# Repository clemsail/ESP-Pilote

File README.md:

# ESP-Pilote

Ceci est un projet autor d'esp easy pour gérer un fil pilote de chauffage en wifi 
avec capteur de temperature, capteur de courant et ES deportée

liste composant :
1x Alim 3.3v HLK-PM03
http://www.ebay.fr/itm/252533336629?_trksid=p2057872.m2749.l2649

1x ESP8266 12e
1x Fusible 500mA (exemple : http://fr.farnell.com/multicomp/mst-500ma-250v/fusible-radial-action-lente-bbas/dp/1566097)

2x Diode 1N4007
2x optotriac TLP168J

1x capteur de courant 
ALLEGRO MICROSYSTEMS - ACS758LCB-050B-PFF-T - IC, ACTUEL CAPTEUR, 50A, 3CB

1x condensateur 0.1µF
1x resistance 4.7k
2x resistance 470
1x capteur de temperature dallas ds18b20

des pinoche ecartement 2.54

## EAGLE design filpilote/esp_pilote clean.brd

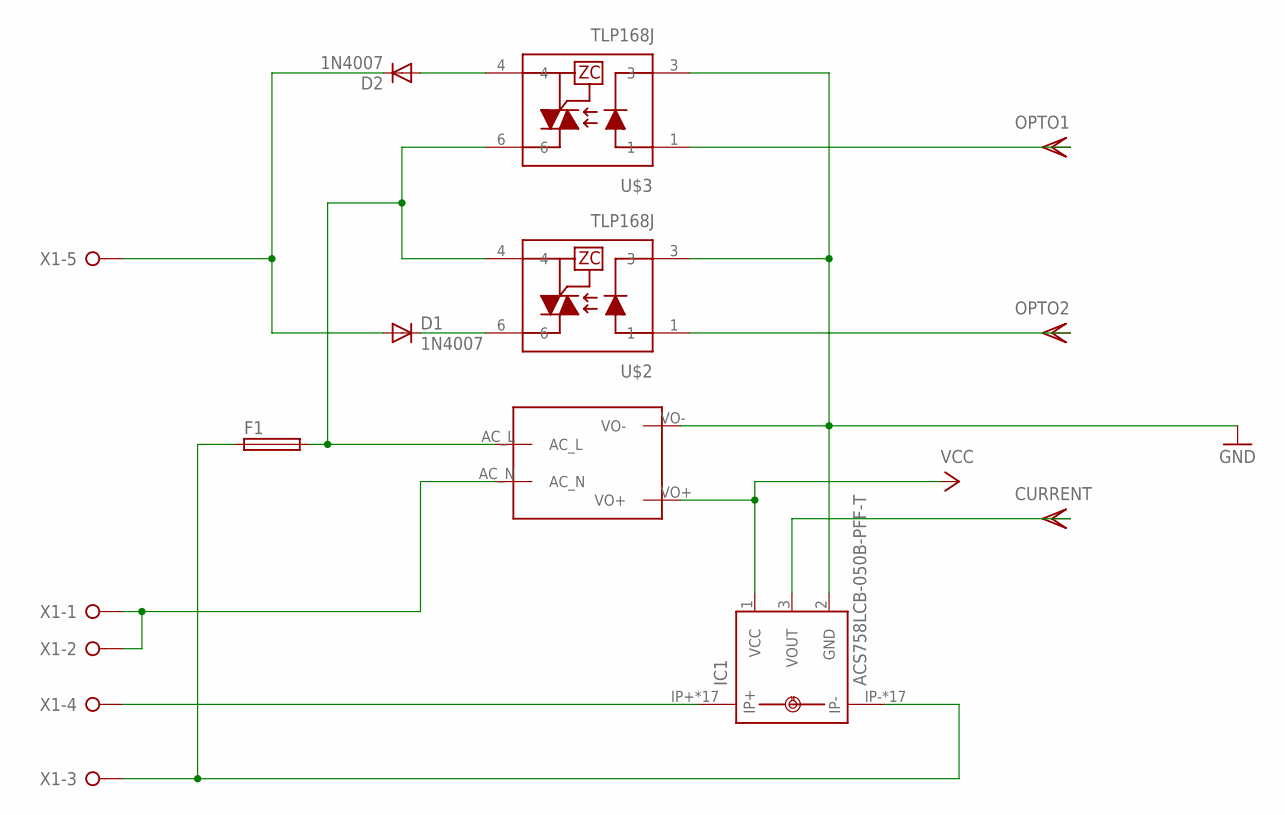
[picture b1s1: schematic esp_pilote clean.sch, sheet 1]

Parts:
D1, D2: 1N4007; DO41-10
F1: 19560
IC1: ACS758LCB-050B-PFF-T; CB-PFF
U$1: MAINS_CONVERTERS; HLK-PM01
U$2, U$3: TLP168J; MFSOP-4
X1: W237-05P; W237-5P

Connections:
230FUSED: F1.2, U$1.AC_L, U$2.4, U$3.6
230OUT: F1.1, IC1.IP-, IC1.IP-@2 (IP-), IC1.IP-@3 (IP-), IC1.IP-@4 (IP-), IC1.IP-@5 (IP-), IC1.IP-@6 (IP-), IC1.IP-@7 (IP-), IC1.IP-@8 (IP-), IC1.IP-@9 (IP-), IC1.IP-@10 (IP-), IC1.IP-@11 (IP-), IC1.IP-@12 (IP-), IC1.IP-@13 (IP-), IC1.IP-@14 (IP-), IC1.IP-@15 (IP-), IC1.IP-@16 (IP-), IC1.IP-@17 (IP-), X1.3
CURENT: IC1.3 (VOUT); also elsewhere on the board
GND: IC1.2 (GND), U$1.VO-, U$2.3, U$3.3; also elsewhere on the board
unnamed: IC1.IP+, IC1.IP+@2 (IP+), IC1.IP+@3 (IP+), IC1.IP+@4 (IP+), IC1.IP+@5 (IP+), IC1.IP+@6 (IP+), IC1.IP+@7 (IP+), IC1.IP+@8 (IP+), IC1.IP+@9 (IP+), IC1.IP+@10 (IP+), IC1.IP+@11 (IP+), IC1.IP+@12 (IP+), IC1.IP+@13 (IP+), IC1.IP+@14 (IP+), IC1.IP+@15 (IP+), IC1.IP+@16 (IP+), IC1.IP+@17 (IP+), X1.4
NEUTRAL: U$1.AC_N, X1.1, X1.2
OPTO1: U$3.1; also elsewhere on the board
OPTO2: U$2.1; also elsewhere on the board
OPTO_O1: D2.A, U$3.4
OPTO_O2: D1.C, U$2.6
PILOTE: D1.A, D2.C, X1.5
VCC: IC1.1 (VCC), U$1.VO+; also elsewhere on the board

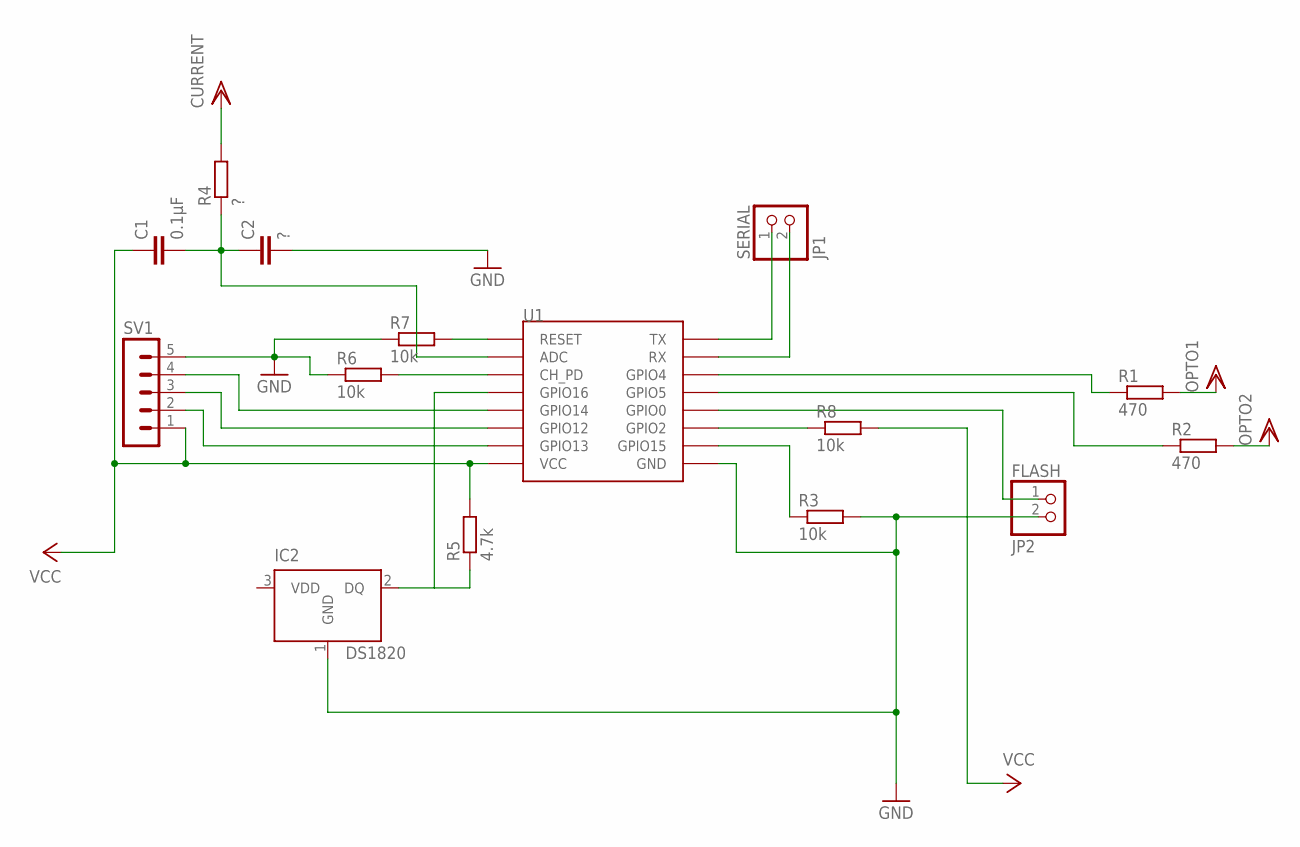
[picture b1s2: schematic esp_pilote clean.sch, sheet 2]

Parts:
C1: 0.1µF; C5B3.5
C2: ?; C5B3.5
FLASH: JP2; 1X02
IC2: DS1820; TO-92
R1, R2: 470; 0207/10
R3, R6, R7, R8: 10k; 0207/10
R4: ?; 0207/10
R5: 4.7k; 0207/10
SERIAL: JP1; 1X02
SV1: MA05-1
U1: ESP12SMD; ESP12-SMD

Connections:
CH_PD: R6.2, U1.CH_PD
CURENT: R4.2; also elsewhere on the board
CURRENT: C1.2, C2.1, R4.1, U1.ADC
DS18B20: IC2.2 (DQ), R5.1, U1.GPIO16
GND: C2.2, FLASH.2, IC2.1 (GND), R3.2, R6.1, R7.1, SV1.5, U1.GND; also elsewhere on the board
GP12: SV1.3, U1.GPIO12
GP13: SV1.2, U1.GPIO13
GP14: SV1.4, U1.GPIO14
unnamed: SERIAL.1, U1.TXD0 (TX)
unnamed: SERIAL.2, U1.RXD0 (RX)
unnamed: FLASH.1, U1.GPIO0
unnamed: R3.1, U1.GPIO15
unnamed: R8.1, U1.GPIO2
OPTO1: R1.2; also elsewhere on the board
OPTO1_OUT: R1.1, U1.GPIO4
OPTO2: R2.2; also elsewhere on the board
OPTO2_OUT: R2.1, U1.GPIO5
RST: R7.2, U1.RESET
VCC: C1.1, R5.2, R8.2, SV1.1, U1.VCC; also elsewhere on the board

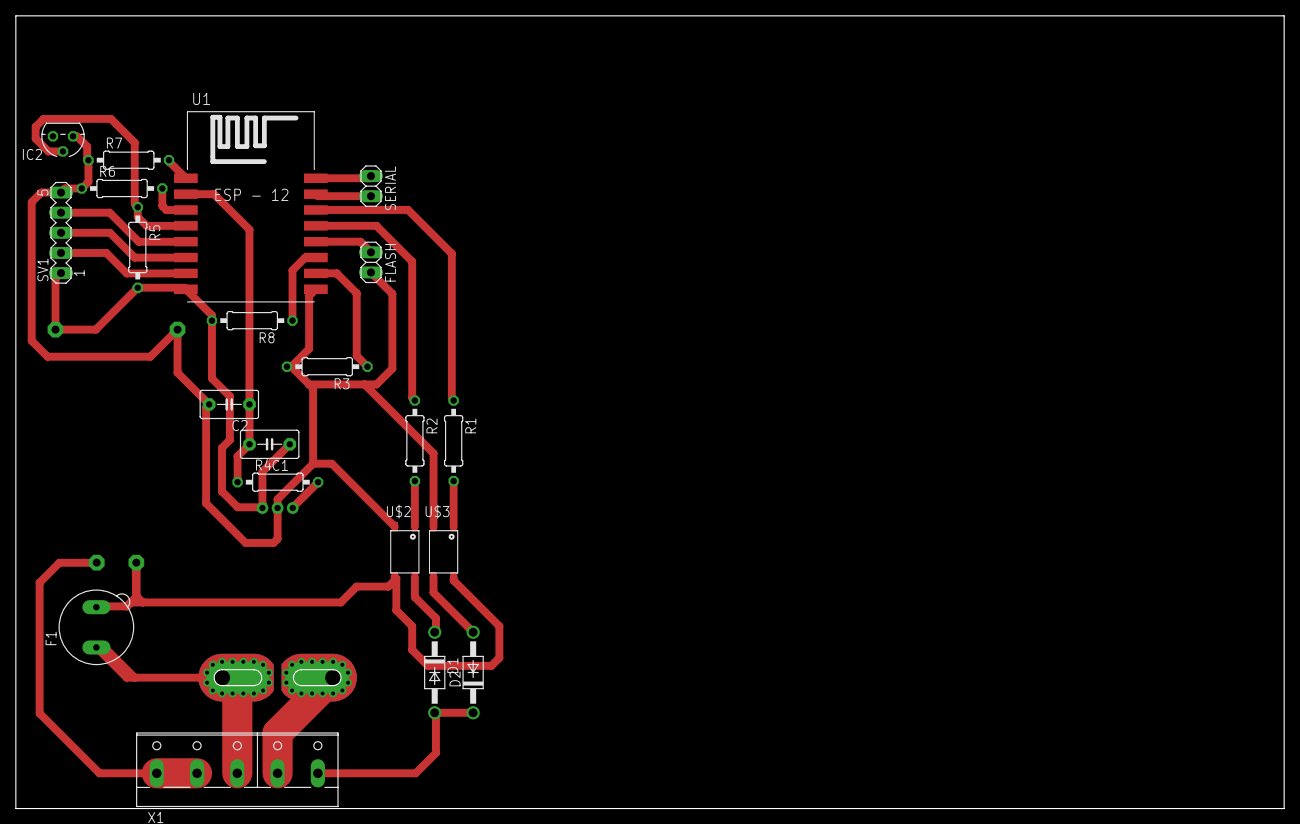
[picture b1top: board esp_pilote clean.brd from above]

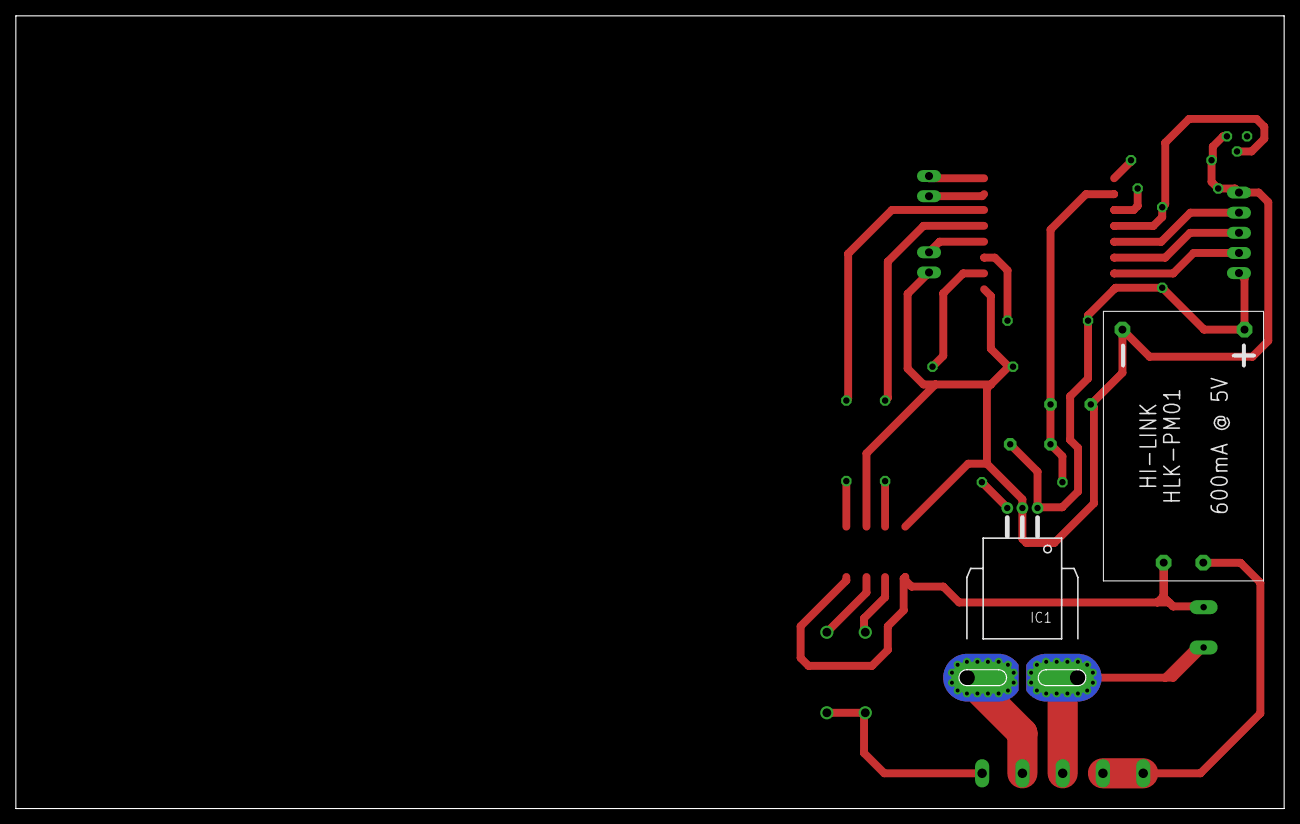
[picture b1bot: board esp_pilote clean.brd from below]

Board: 2 copper layers, 160.0 x 100.0 mm, 23 parts (2 on the bottom side), 26 nets.

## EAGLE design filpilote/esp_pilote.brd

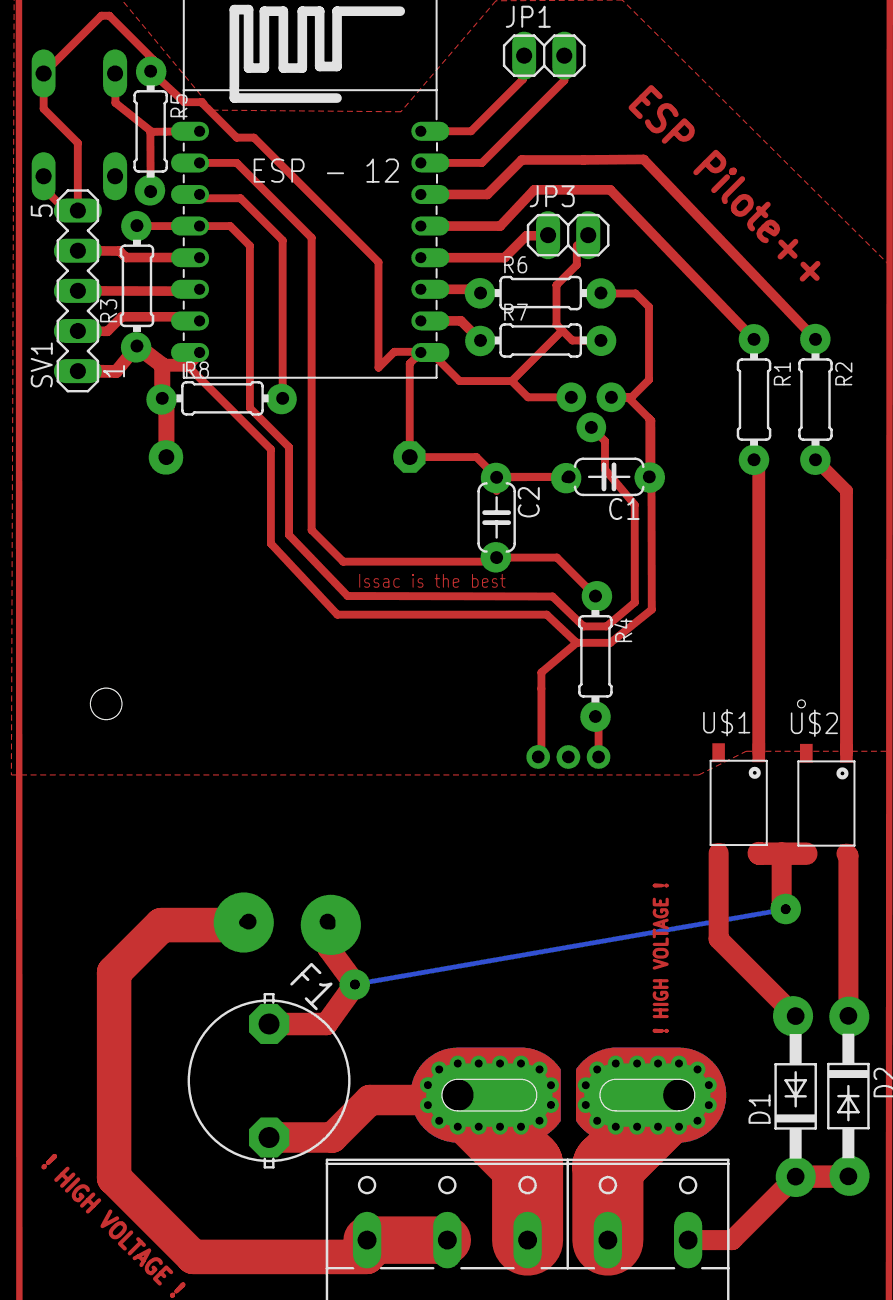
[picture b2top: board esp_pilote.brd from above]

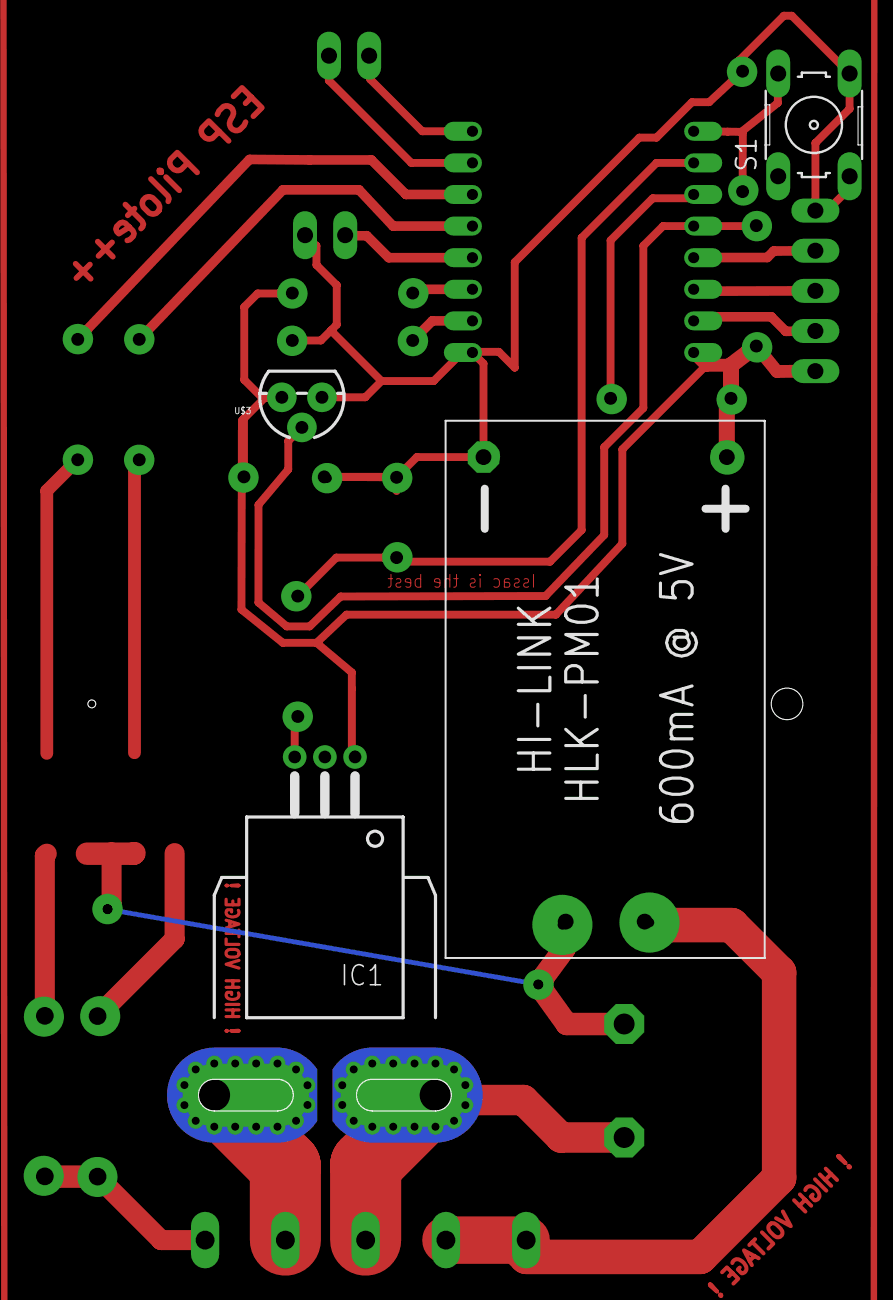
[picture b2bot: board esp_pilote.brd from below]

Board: 2 copper layers, 24 parts (4 on the bottom side), 26 nets.

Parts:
C1: 0,1µf; C050-024X044
C2: ?; C050-024X044
D1, D2: 1N4007; DO41-10
F1: 0,5A; 19559
IC1: ACS758LCB-050B-PFF-T; CB-PFF
JP1, JP3: 1X02
MDL1: ESP; ESP12
R1, R2: 470; 0204/7
R3: 4.7k; 0204/7
R4: ?; 0204/7
R5, R6, R7, R8: 10k; 0204/7
S1: B3F-10XX
SV1: MA05-1
U$1, U$2: TLP168J; MFSOP-4
U$3: TEMPERATURE-SENSOR; TO-92
U$4: MAINS_CONVERTERS; HLK-PM01
X1: W237-5P

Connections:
230FUSED: F1.1, U$1.6, U$2.4, U$4.AC_L
230IN: F1.2, IC1.IP-, IC1.IP-@2, IC1.IP-@3, IC1.IP-@4, IC1.IP-@5, IC1.IP-@6, IC1.IP-@7, IC1.IP-@8, IC1.IP-@9, IC1.IP-@10, IC1.IP-@11, IC1.IP-@12, IC1.IP-@13, IC1.IP-@14, IC1.IP-@15, IC1.IP-@16, IC1.IP-@17, X1.3
230OUT: IC1.IP+, IC1.IP+@2, IC1.IP+@3, IC1.IP+@4, IC1.IP+@5, IC1.IP+@6, IC1.IP+@7, IC1.IP+@8, IC1.IP+@9, IC1.IP+@10, IC1.IP+@11, IC1.IP+@12, IC1.IP+@13, IC1.IP+@14, IC1.IP+@15, IC1.IP+@16, IC1.IP+@17, X1.4
CURRENT: C2.2, MDL1.ADC, R4.1
DS18B20: MDL1.GPIO16, R3.2, U$3.2
GND: C1.2, C2.1, IC1.2, JP3.2, MDL1.GND, R5.1, R7.2, S1.3, S1.4, SV1.5, U$1.3, U$2.3, U$3.1, U$4.VO-
unnamed: D2.C, U$2.6
unnamed: R1.2, U$1.1
unnamed: IC1.3, R4.2
unnamed: D1.A, U$1.4
unnamed: MDL1.GPIO13, SV1.2
unnamed: MDL1.GPIO12, SV1.3
unnamed: MDL1.GPIO14, SV1.4
unnamed: R2.2, U$2.1
unnamed: MDL1.GPIO5, R1.1
unnamed: MDL1.GPIO4, R2.1
unnamed: MDL1.RESET, R5.2, S1.2
unnamed: JP1.1, MDL1.TX
unnamed: JP1.2, MDL1.RX
unnamed: MDL1.CH_PD, R8.2
unnamed: MDL1.GPIO2, R6.1
unnamed: MDL1.GPIO15, R7.1
unnamed: JP3.1, MDL1.GPIO0
NEUTRAL: U$4.AC_N, X1.1, X1.2
PILOTE: D1.C, D2.A, X1.5
VCC: C1.1, IC1.1, MDL1.VCC, R3.1, R6.2, R8.1, SV1.1, U$3.3, U$4.VO+

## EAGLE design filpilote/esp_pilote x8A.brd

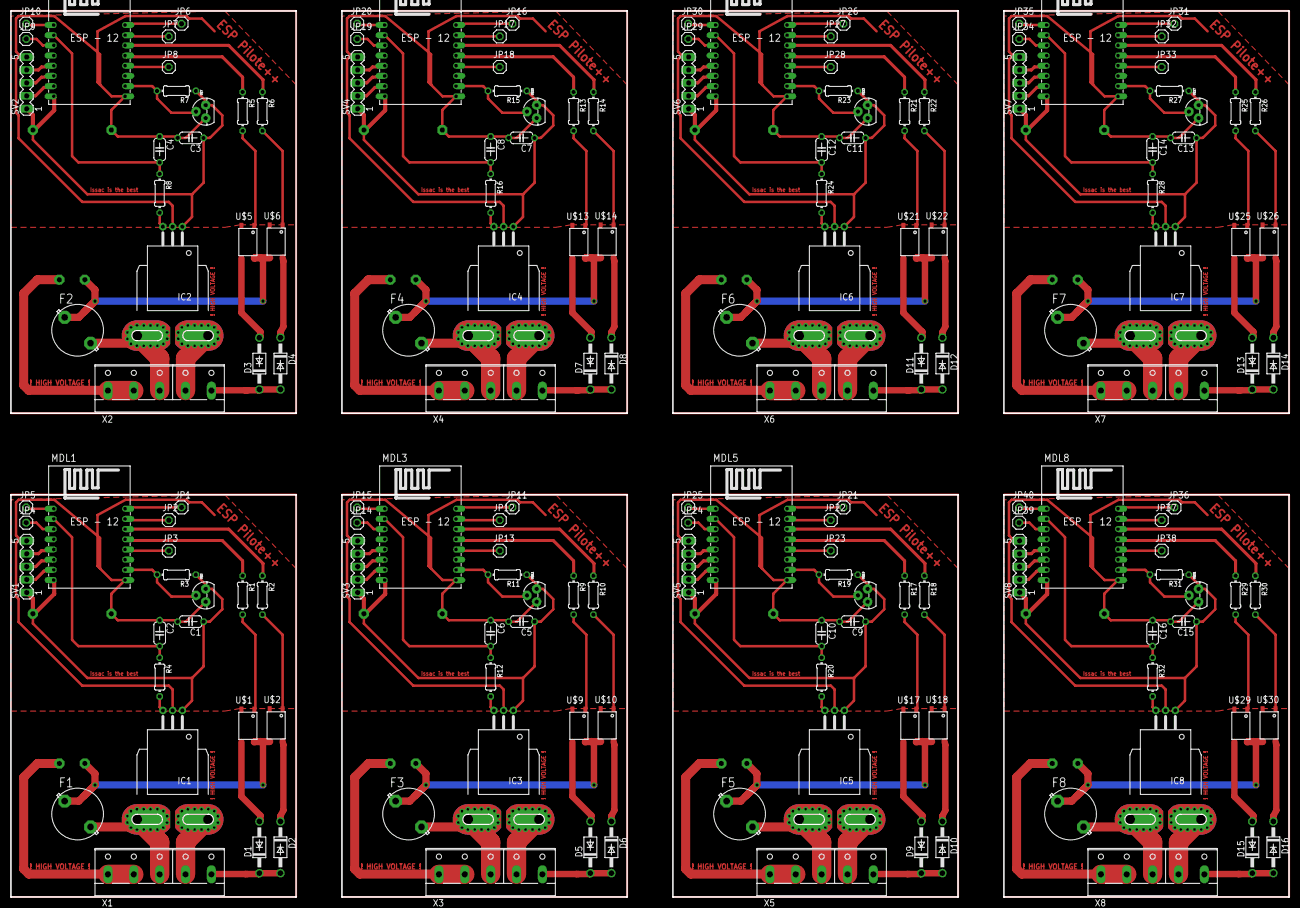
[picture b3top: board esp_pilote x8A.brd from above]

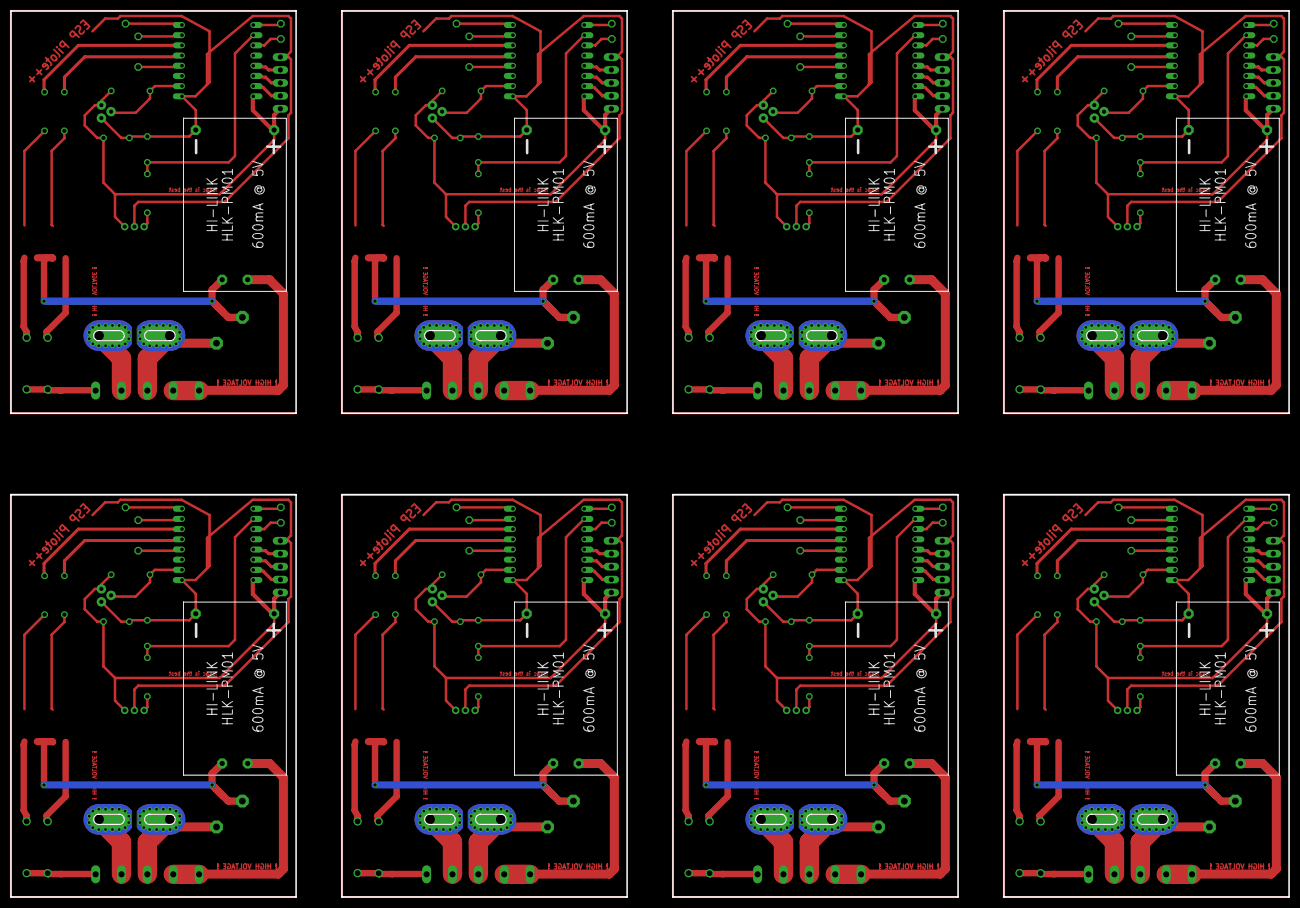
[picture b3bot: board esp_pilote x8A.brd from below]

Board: 2 copper layers, 251.0 x 174.0 mm, 176 parts (8 on the bottom side), 192 nets.

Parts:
C1, C3, C5, C7, C9, C11, C13, C15: 0,1µf; C050-024X044
C2, C4, C6, C8, C10, C12, C14, C16: ?; C050-024X044
D1, D2, D3, D4, D5, D6, D7, D8, D9, D10, D11, D12, D13, D14, D15, D16: 1N4007; DO41-10
F1, F2, F3, F4, F5, F6, F7, F8: 0,5A; 19559
IC1, IC2, IC3, IC4, IC5, IC6, IC7, IC8: ACS758LCB-050B-PFF-T; CB-PFF
JP1, JP2, JP3, JP4, JP5, JP6, JP7, JP8, JP9, JP10, JP11, JP12, JP13, JP14, JP15, JP16, JP17, JP18, JP19, JP20, JP21, JP22, JP23, JP24, JP25, JP26, JP27, JP28, JP29, JP30, JP31, JP32, JP33, JP34, JP35, JP36, JP37, JP38, JP39, JP40: 1X01
MDL1, MDL2, MDL3, MDL4, MDL5, MDL6, MDL7, MDL8: ESP; ESP12
R1, R2, R5, R6, R9, R10, R13, R14, R17, R18, R21, R22, R25, R26, R29, R30: 470; 0204/7
R3, R7, R11, R15, R19, R23, R27, R31: 4.7k; 0204/7
R4, R8, R12, R16, R20, R24, R28, R32: ?; 0204/7
SV1, SV2, SV3, SV4, SV5, SV6, SV7, SV8: MA05-1
U$1, U$2, U$5, U$6, U$9, U$10, U$13, U$14, U$17, U$18, U$21, U$22, U$25, U$26, U$29, U$30: TLP168J; MFSOP-4
U$3, U$7, U$11, U$15, U$19, U$23, U$27, U$31: TEMPERATURE-SENSOR; TO-92
U$4, U$8, U$12, U$16, U$20, U$24, U$28, U$32: MAINS_CONVERTERS; HLK-PM01
X1, X2, X3, X4, X5, X6, X7, X8: W237-5P

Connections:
230FUSED: F1.1, U$1.6, U$2.4, U$4.AC_L
230FUSED1: F2.1, U$5.6, U$6.4, U$8.AC_L
230FUSED2: F3.1, U$9.6, U$10.4, U$12.AC_L
230FUSED3: F4.1, U$13.6, U$14.4, U$16.AC_L
230FUSED4: F5.1, U$17.6, U$18.4, U$20.AC_L
230FUSED5: F6.1, U$21.6, U$22.4, U$24.AC_L
230FUSED6: F7.1, U$25.6, U$26.4, U$28.AC_L
230FUSED7: F8.1, U$29.6, U$30.4, U$32.AC_L
230IN: F1.2, IC1.IP+, IC1.IP+@2, IC1.IP+@3, IC1.IP+@4, IC1.IP+@5, IC1.IP+@6, IC1.IP+@7, IC1.IP+@8, IC1.IP+@9, IC1.IP+@10, IC1.IP+@11, IC1.IP+@12, IC1.IP+@13, IC1.IP+@14, IC1.IP+@15, IC1.IP+@16, IC1.IP+@17, X1.3
230IN1: F2.2, IC2.IP+, IC2.IP+@2, IC2.IP+@3, IC2.IP+@4, IC2.IP+@5, IC2.IP+@6, IC2.IP+@7, IC2.IP+@8, IC2.IP+@9, IC2.IP+@10, IC2.IP+@11, IC2.IP+@12, IC2.IP+@13, IC2.IP+@14, IC2.IP+@15, IC2.IP+@16, IC2.IP+@17, X2.3
230IN2: F3.2, IC3.IP+, IC3.IP+@2, IC3.IP+@3, IC3.IP+@4, IC3.IP+@5, IC3.IP+@6, IC3.IP+@7, IC3.IP+@8, IC3.IP+@9, IC3.IP+@10, IC3.IP+@11, IC3.IP+@12, IC3.IP+@13, IC3.IP+@14, IC3.IP+@15, IC3.IP+@16, IC3.IP+@17, X3.3
230IN3: F4.2, IC4.IP+, IC4.IP+@2, IC4.IP+@3, IC4.IP+@4, IC4.IP+@5, IC4.IP+@6, IC4.IP+@7, IC4.IP+@8, IC4.IP+@9, IC4.IP+@10, IC4.IP+@11, IC4.IP+@12, IC4.IP+@13, IC4.IP+@14, IC4.IP+@15, IC4.IP+@16, IC4.IP+@17, X4.3
230IN4: F5.2, IC5.IP+, IC5.IP+@2, IC5.IP+@3, IC5.IP+@4, IC5.IP+@5, IC5.IP+@6, IC5.IP+@7, IC5.IP+@8, IC5.IP+@9, IC5.IP+@10, IC5.IP+@11, IC5.IP+@12, IC5.IP+@13, IC5.IP+@14, IC5.IP+@15, IC5.IP+@16, IC5.IP+@17, X5.3
230IN5: F6.2, IC6.IP+, IC6.IP+@2, IC6.IP+@3, IC6.IP+@4, IC6.IP+@5, IC6.IP+@6, IC6.IP+@7, IC6.IP+@8, IC6.IP+@9, IC6.IP+@10, IC6.IP+@11, IC6.IP+@12, IC6.IP+@13, IC6.IP+@14, IC6.IP+@15, IC6.IP+@16, IC6.IP+@17, X6.3
230IN6: F7.2, IC7.IP+, IC7.IP+@2, IC7.IP+@3, IC7.IP+@4, IC7.IP+@5, IC7.IP+@6, IC7.IP+@7, IC7.IP+@8, IC7.IP+@9, IC7.IP+@10, IC7.IP+@11, IC7.IP+@12, IC7.IP+@13, IC7.IP+@14, IC7.IP+@15, IC7.IP+@16, IC7.IP+@17, X7.3
230IN7: F8.2, IC8.IP+, IC8.IP+@2, IC8.IP+@3, IC8.IP+@4, IC8.IP+@5, IC8.IP+@6, IC8.IP+@7, IC8.IP+@8, IC8.IP+@9, IC8.IP+@10, IC8.IP+@11, IC8.IP+@12, IC8.IP+@13, IC8.IP+@14, IC8.IP+@15, IC8.IP+@16, IC8.IP+@17, X8.3
230OUT: IC1.IP-, IC1.IP-@2, IC1.IP-@3, IC1.IP-@4, IC1.IP-@5, IC1.IP-@6, IC1.IP-@7, IC1.IP-@8, IC1.IP-@9, IC1.IP-@10, IC1.IP-@11, IC1.IP-@12, IC1.IP-@13, IC1.IP-@14, IC1.IP-@15, IC1.IP-@16, IC1.IP-@17, X1.4
230OUT1: IC2.IP-, IC2.IP-@2, IC2.IP-@3, IC2.IP-@4, IC2.IP-@5, IC2.IP-@6, IC2.IP-@7, IC2.IP-@8, IC2.IP-@9, IC2.IP-@10, IC2.IP-@11, IC2.IP-@12, IC2.IP-@13, IC2.IP-@14, IC2.IP-@15, IC2.IP-@16, IC2.IP-@17, X2.4
230OUT2: IC3.IP-, IC3.IP-@2, IC3.IP-@3, IC3.IP-@4, IC3.IP-@5, IC3.IP-@6, IC3.IP-@7, IC3.IP-@8, IC3.IP-@9, IC3.IP-@10, IC3.IP-@11, IC3.IP-@12, IC3.IP-@13, IC3.IP-@14, IC3.IP-@15, IC3.IP-@16, IC3.IP-@17, X3.4
230OUT3: IC4.IP-, IC4.IP-@2, IC4.IP-@3, IC4.IP-@4, IC4.IP-@5, IC4.IP-@6, IC4.IP-@7, IC4.IP-@8, IC4.IP-@9, IC4.IP-@10, IC4.IP-@11, IC4.IP-@12, IC4.IP-@13, IC4.IP-@14, IC4.IP-@15, IC4.IP-@16, IC4.IP-@17, X4.4
230OUT4: IC5.IP-, IC5.IP-@2, IC5.IP-@3, IC5.IP-@4, IC5.IP-@5, IC5.IP-@6, IC5.IP-@7, IC5.IP-@8, IC5.IP-@9, IC5.IP-@10, IC5.IP-@11, IC5.IP-@12, IC5.IP-@13, IC5.IP-@14, IC5.IP-@15, IC5.IP-@16, IC5.IP-@17, X5.4
230OUT5: IC6.IP-, IC6.IP-@2, IC6.IP-@3, IC6.IP-@4, IC6.IP-@5, IC6.IP-@6, IC6.IP-@7, IC6.IP-@8, IC6.IP-@9, IC6.IP-@10, IC6.IP-@11, IC6.IP-@12, IC6.IP-@13, IC6.IP-@14, IC6.IP-@15, IC6.IP-@16, IC6.IP-@17, X6.4
230OUT6: IC7.IP-, IC7.IP-@2, IC7.IP-@3, IC7.IP-@4, IC7.IP-@5, IC7.IP-@6, IC7.IP-@7, IC7.IP-@8, IC7.IP-@9, IC7.IP-@10, IC7.IP-@11, IC7.IP-@12, IC7.IP-@13, IC7.IP-@14, IC7.IP-@15, IC7.IP-@16, IC7.IP-@17, X7.4
230OUT7: IC8.IP-, IC8.IP-@2, IC8.IP-@3, IC8.IP-@4, IC8.IP-@5, IC8.IP-@6, IC8.IP-@7, IC8.IP-@8, IC8.IP-@9, IC8.IP-@10, IC8.IP-@11, IC8.IP-@12, IC8.IP-@13, IC8.IP-@14, IC8.IP-@15, IC8.IP-@16, IC8.IP-@17, X8.4
CURRENT: C2.2, MDL1.ADC, R4.1
CURRENT1: C4.2, MDL2.ADC, R8.1
CURRENT2: C6.2, MDL3.ADC, R12.1
CURRENT3: C8.2, MDL4.ADC, R16.1
CURRENT4: C10.2, MDL5.ADC, R20.1
CURRENT5: C12.2, MDL6.ADC, R24.1
CURRENT6: C14.2, MDL7.ADC, R28.1
CURRENT7: C16.2, MDL8.ADC, R32.1
GND: C1.2, C2.1, IC1.2, MDL1.GND, SV1.5, U$1.3, U$2.3, U$3.1, U$4.VO-
GND1: C3.2, C4.1, IC2.2, MDL2.GND, SV2.5, U$5.3, U$6.3, U$7.1, U$8.VO-
GND2: C5.2, C6.1, IC3.2, MDL3.GND, SV3.5, U$9.3, U$10.3, U$11.1, U$12.VO-
GND3: C7.2, C8.1, IC4.2, MDL4.GND, SV4.5, U$13.3, U$14.3, U$15.1, U$16.VO-
GND4: C9.2, C10.1, IC5.2, MDL5.GND, SV5.5, U$17.3, U$18.3, U$19.1, U$20.VO-
GND5: C11.2, C12.1, IC6.2, MDL6.GND, SV6.5, U$21.3, U$22.3, U$23.1, U$24.VO-
GND6: C13.2, C14.1, IC7.2, MDL7.GND, SV7.5, U$25.3, U$26.3, U$27.1, U$28.VO-
GND7: C15.2, C16.1, IC8.2, MDL8.GND, SV8.5, U$29.3, U$30.3, U$31.1, U$32.VO-
unnamed: D2.C, U$2.6
unnamed: R1.2, U$1.1
unnamed: IC1.3, R4.2
unnamed: D1.A, U$1.4
unnamed: MDL1.GPIO13, SV1.2
unnamed: MDL1.GPIO12, SV1.3
unnamed: MDL1.GPIO14, SV1.4
unnamed: R2.2, U$2.1
unnamed: MDL1.GPIO15, R3.2, U$3.2
unnamed: MDL1.GPIO5, R1.1
unnamed: MDL1.GPIO4, R2.1
unnamed: JP4.1, MDL1.CH_PD
unnamed: JP1.1, MDL1.TX
unnamed: JP2.1, MDL1.RX
unnamed: JP3.1, MDL1.GPIO0
unnamed: JP5.1, MDL1.RESET
unnamed: R5.2, U$5.1
unnamed: R6.2, U$6.1
unnamed: IC2.3, R8.2
unnamed: D3.A, U$5.4
unnamed: D4.C, U$6.6
unnamed: MDL2.GPIO13, SV2.2
unnamed: MDL2.GPIO12, SV2.3
unnamed: MDL2.GPIO14, SV2.4
unnamed: MDL2.GPIO15, R7.2, U$7.2
unnamed: MDL2.GPIO5, R5.1
unnamed: MDL2.GPIO4, R6.1
unnamed: JP9.1, MDL2.CH_PD
unnamed: JP6.1, MDL2.TX
unnamed: JP7.1, MDL2.RX
unnamed: JP8.1, MDL2.GPIO0
unnamed: JP10.1, MDL2.RESET
unnamed: R9.2, U$9.1
unnamed: R10.2, U$10.1
unnamed: IC3.3, R12.2
unnamed: D5.A, U$9.4
unnamed: D6.C, U$10.6
unnamed: MDL3.GPIO13, SV3.2
unnamed: MDL3.GPIO12, SV3.3
unnamed: MDL3.GPIO14, SV3.4
unnamed: MDL3.GPIO15, R11.2, U$11.2
unnamed: MDL3.GPIO5, R9.1
unnamed: MDL3.GPIO4, R10.1
unnamed: JP14.1, MDL3.CH_PD
unnamed: JP11.1, MDL3.TX
unnamed: JP12.1, MDL3.RX
unnamed: JP13.1, MDL3.GPIO0
unnamed: JP15.1, MDL3.RESET
unnamed: R13.2, U$13.1
unnamed: R14.2, U$14.1
unnamed: IC4.3, R16.2
unnamed: D7.A, U$13.4
unnamed: D8.C, U$14.6
unnamed: MDL4.GPIO13, SV4.2
unnamed: MDL4.GPIO12, SV4.3
unnamed: MDL4.GPIO14, SV4.4
unnamed: MDL4.GPIO15, R15.2, U$15.2
unnamed: MDL4.GPIO5, R13.1
unnamed: MDL4.GPIO4, R14.1
unnamed: JP19.1, MDL4.CH_PD
unnamed: JP16.1, MDL4.TX
unnamed: JP17.1, MDL4.RX
unnamed: JP18.1, MDL4.GPIO0
unnamed: JP20.1, MDL4.RESET
unnamed: R17.2, U$17.1
unnamed: R18.2, U$18.1
unnamed: IC5.3, R20.2
unnamed: D9.A, U$17.4
unnamed: D10.C, U$18.6
unnamed: MDL5.GPIO13, SV5.2
unnamed: MDL5.GPIO12, SV5.3
unnamed: MDL5.GPIO14, SV5.4
unnamed: MDL5.GPIO15, R19.2, U$19.2
unnamed: MDL5.GPIO5, R17.1
unnamed: MDL5.GPIO4, R18.1
unnamed: JP24.1, MDL5.CH_PD
unnamed: JP21.1, MDL5.TX
unnamed: JP22.1, MDL5.RX
unnamed: JP23.1, MDL5.GPIO0
unnamed: JP25.1, MDL5.RESET
unnamed: R21.2, U$21.1
unnamed: R22.2, U$22.1
unnamed: IC6.3, R24.2
unnamed: D11.A, U$21.4
unnamed: D12.C, U$22.6
unnamed: MDL6.GPIO13, SV6.2
unnamed: MDL6.GPIO12, SV6.3
unnamed: MDL6.GPIO14, SV6.4
unnamed: MDL6.GPIO15, R23.2, U$23.2
unnamed: MDL6.GPIO5, R21.1
unnamed: MDL6.GPIO4, R22.1
unnamed: JP29.1, MDL6.CH_PD
unnamed: JP26.1, MDL6.TX
unnamed: JP27.1, MDL6.RX
unnamed: JP28.1, MDL6.GPIO0
unnamed: JP30.1, MDL6.RESET
unnamed: R25.2, U$25.1
unnamed: R26.2, U$26.1
unnamed: IC7.3, R28.2
unnamed: D13.A, U$25.4
unnamed: D14.C, U$26.6
unnamed: MDL7.GPIO13, SV7.2
unnamed: MDL7.GPIO12, SV7.3
unnamed: MDL7.GPIO14, SV7.4
unnamed: MDL7.GPIO15, R27.2, U$27.2
unnamed: MDL7.GPIO5, R25.1
unnamed: MDL7.GPIO4, R26.1
unnamed: JP34.1, MDL7.CH_PD
unnamed: JP31.1, MDL7.TX
unnamed: JP32.1, MDL7.RX
unnamed: JP33.1, MDL7.GPIO0
unnamed: JP35.1, MDL7.RESET
unnamed: R29.2, U$29.1
unnamed: R30.2, U$30.1
unnamed: IC8.3, R32.2
unnamed: D15.A, U$29.4
unnamed: D16.C, U$30.6
unnamed: MDL8.GPIO13, SV8.2
unnamed: MDL8.GPIO12, SV8.3
unnamed: MDL8.GPIO14, SV8.4
unnamed: MDL8.GPIO15, R31.2, U$31.2
unnamed: MDL8.GPIO5, R29.1
unnamed: MDL8.GPIO4, R30.1
unnamed: JP39.1, MDL8.CH_PD
unnamed: JP36.1, MDL8.TX
unnamed: JP37.1, MDL8.RX
unnamed: JP38.1, MDL8.GPIO0
unnamed: JP40.1, MDL8.RESET
NEUTRAL: U$4.AC_N, X1.1, X1.2
NEUTRAL1: U$8.AC_N, X2.1, X2.2
NEUTRAL2: U$12.AC_N, X3.1, X3.2
NEUTRAL3: U$16.AC_N, X4.1, X4.2
NEUTRAL4: U$20.AC_N, X5.1, X5.2
NEUTRAL5: U$24.AC_N, X6.1, X6.2
NEUTRAL6: U$28.AC_N, X7.1, X7.2
NEUTRAL7: U$32.AC_N, X8.1, X8.2
PILOTE: D1.C, D2.A, X1.5
PILOTE1: D3.C, D4.A, X2.5
PILOTE2: D5.C, D6.A, X3.5
PILOTE3: D7.C, D8.A, X4.5
PILOTE4: D9.C, D10.A, X5.5
PILOTE5: D11.C, D12.A, X6.5
PILOTE6: D13.C, D14.A, X7.5
PILOTE7: D15.C, D16.A, X8.5
VCC: C1.1, IC1.1, MDL1.VCC, R3.1, SV1.1, U$3.3, U$4.VO+
VCC1: C3.1, IC2.1, MDL2.VCC, R7.1, SV2.1, U$7.3, U$8.VO+
VCC2: C5.1, IC3.1, MDL3.VCC, R11.1, SV3.1, U$11.3, U$12.VO+
VCC3: C7.1, IC4.1, MDL4.VCC, R15.1, SV4.1, U$15.3, U$16.VO+
VCC4: C9.1, IC5.1, MDL5.VCC, R19.1, SV5.1, U$19.3, U$20.VO+
VCC5: C11.1, IC6.1, MDL6.VCC, R23.1, SV6.1, U$23.3, U$24.VO+
VCC6: C13.1, IC7.1, MDL7.VCC, R27.1, SV7.1, U$27.3, U$28.VO+
VCC7: C15.1, IC8.1, MDL8.VCC, R31.1, SV8.1, U$31.3, U$32.VO+

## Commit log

2017-02-10 PCB Ok
2017-02-15 Mise à jour PCB
2017-02-21 Correction pcb
2017-03-07 PCB finale
2017-03-23 Create notepad
2017-03-23 Update notepad
